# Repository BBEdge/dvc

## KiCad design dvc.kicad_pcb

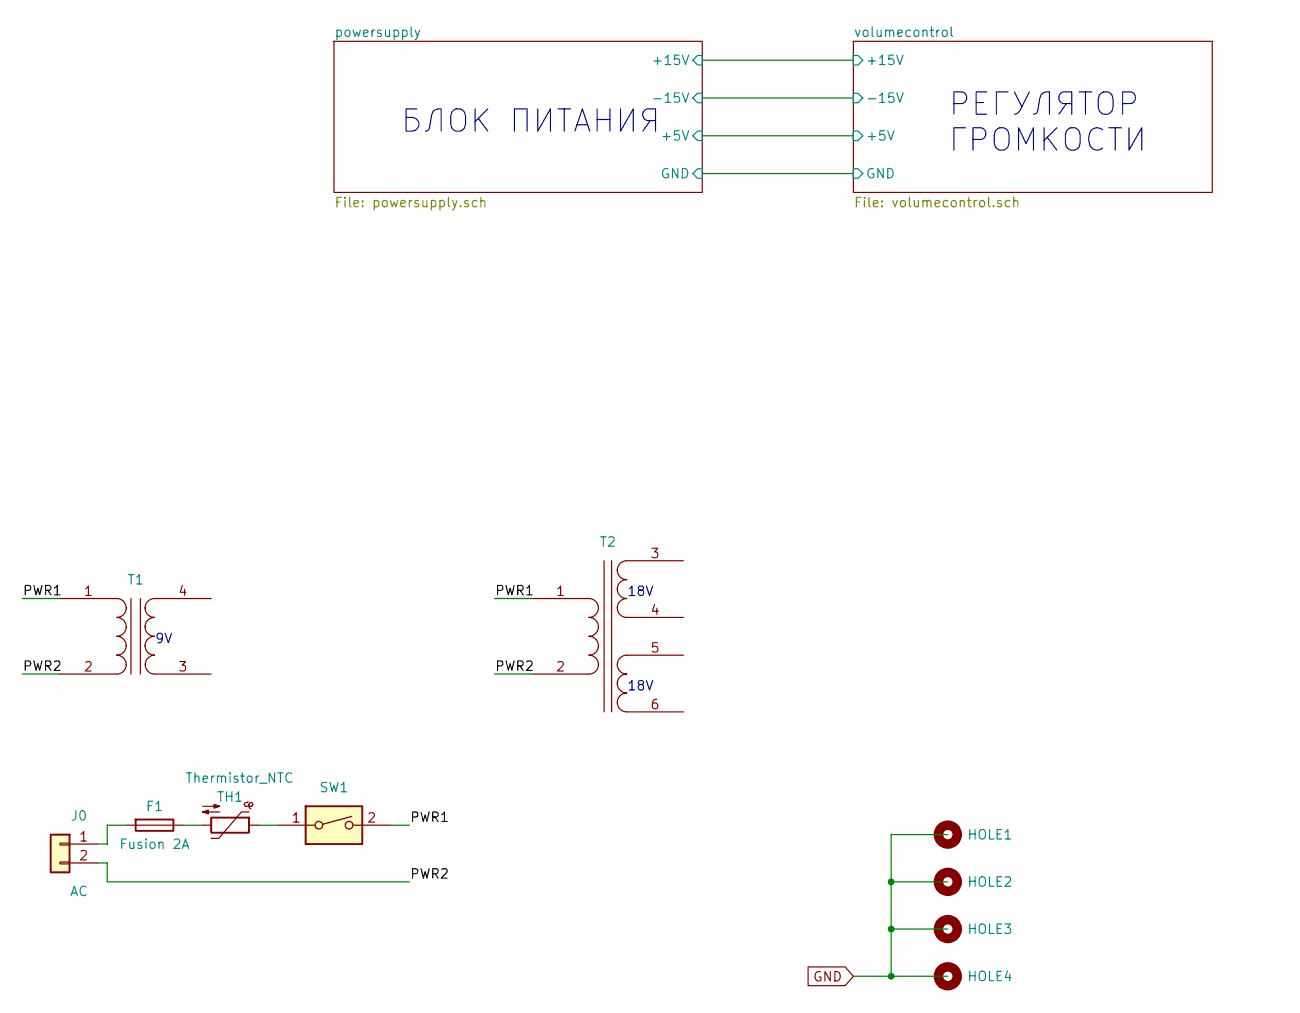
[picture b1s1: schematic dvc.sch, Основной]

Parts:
F1: Fusion 2A
H1: HOLE1; MountingHole_3mm_Pad
H2: HOLE2; MountingHole_3mm_Pad
H3: HOLE3; MountingHole_3mm_Pad
H4: HOLE4; MountingHole_3mm_Pad
J0: AC
SW1: SW_DIP_x01
T1: Transformer_1P_1S
T2: Transformer_1P_2S
TH1: Thermistor_NTC

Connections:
unnamed: F1.1, TH1.2
unnamed: F1.2, J0.1
unnamed: J0.2, T1.2 (AB), T2.2 (AB)
unnamed: SW1.1, TH1.1
unnamed: SW1.2, T1.1 (AA), T2.1 (AA)

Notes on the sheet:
РЕГУЛЯТОР ГРОМКОСТИ
БЛОК ПИТАНИЯ
18V

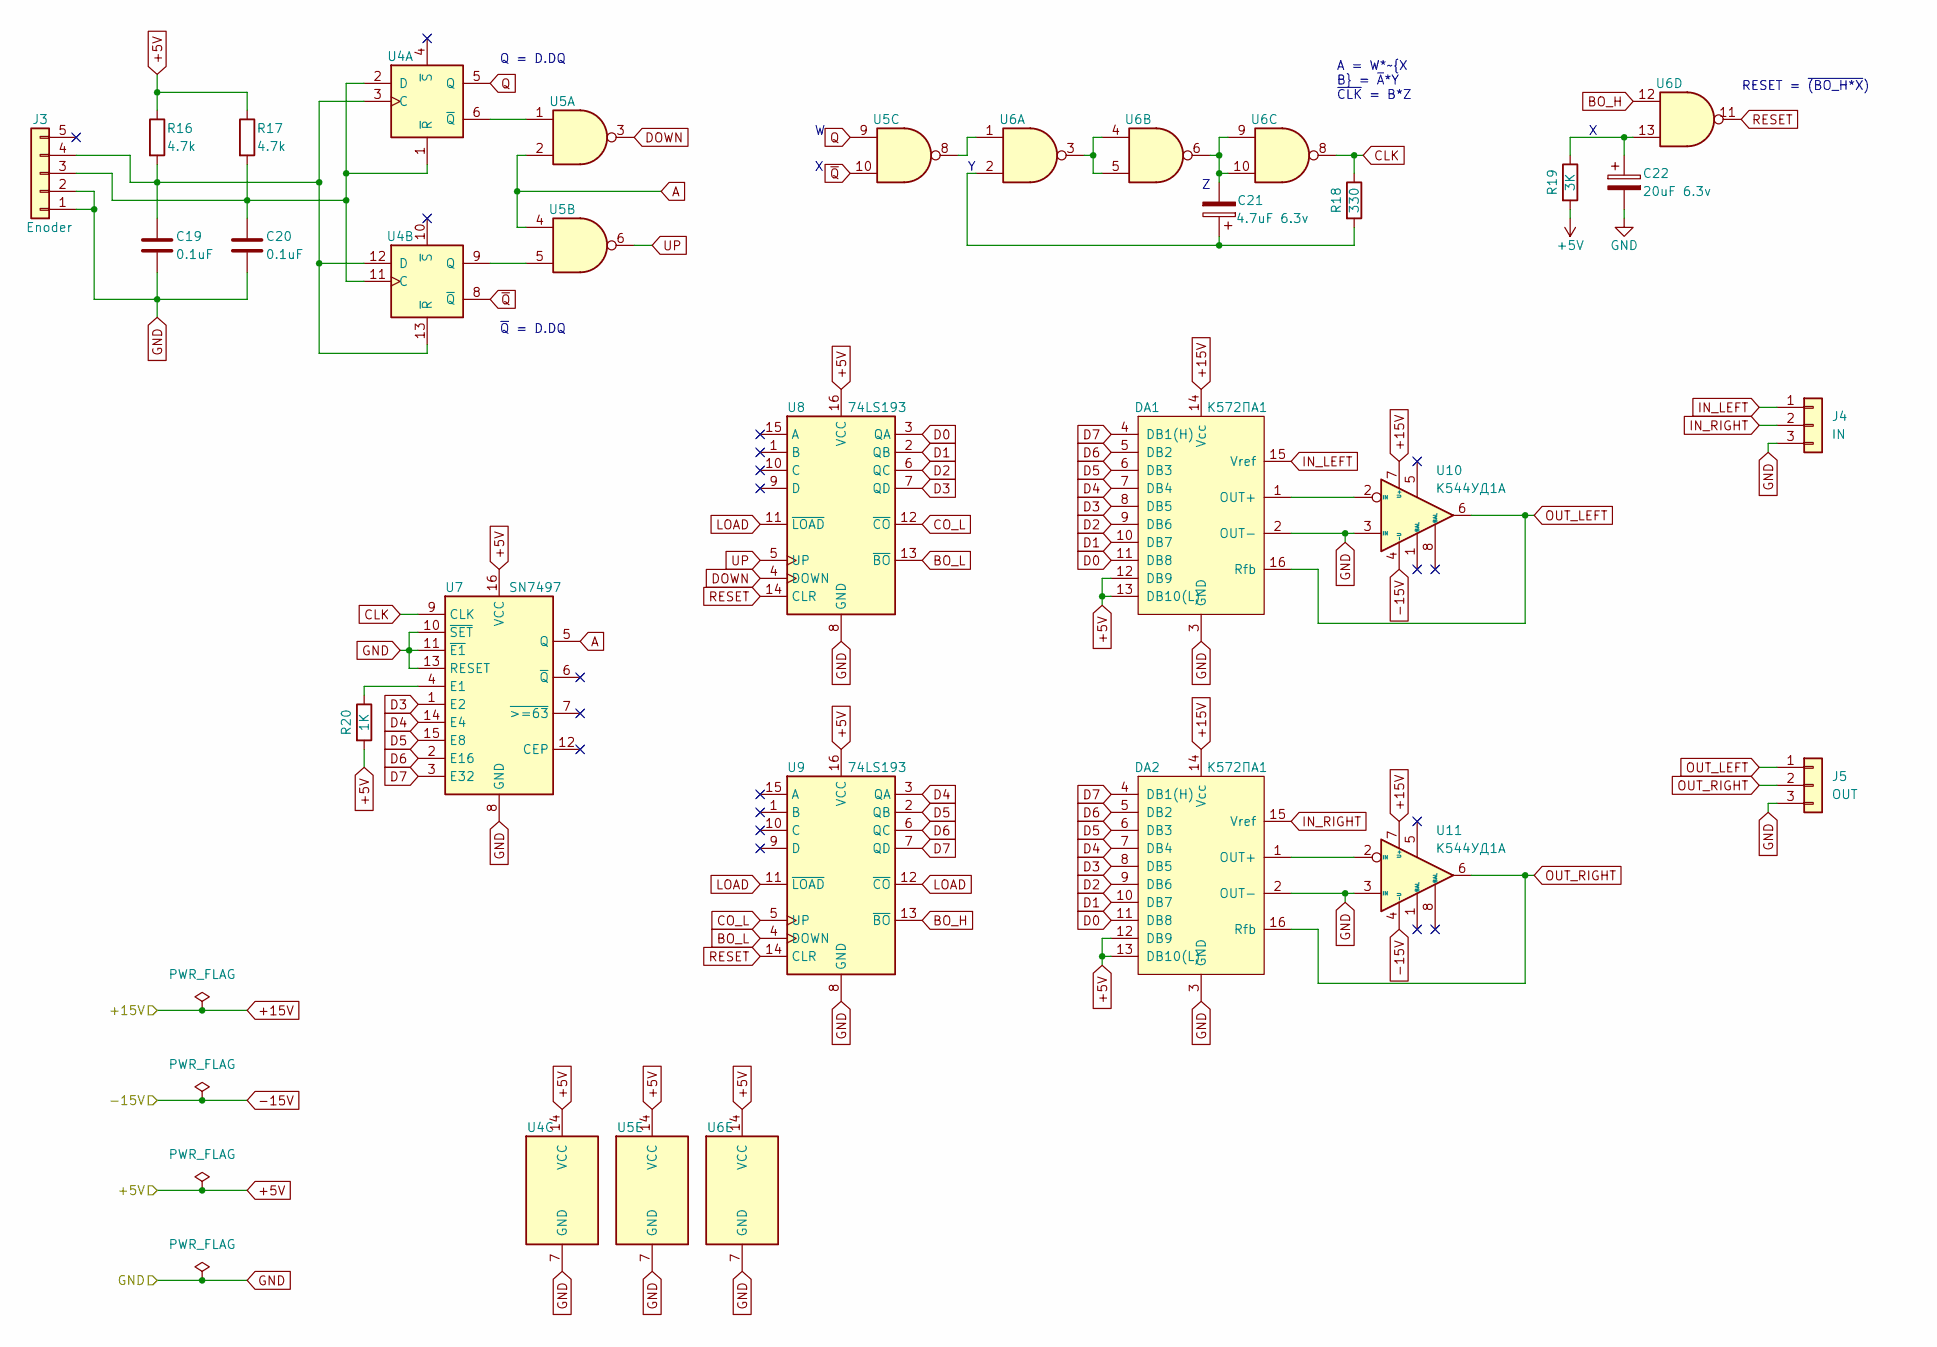
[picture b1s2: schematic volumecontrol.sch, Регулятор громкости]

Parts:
C19, C20: 0.1uF; C_Disc_D4.7mm_W2.5mm_P5.00mm
C21: 4.7uF 6.3v; CP_Radial_D5.0mm_P2.50mm
C22: 20uF 6.3v; CP_Radial_D5.0mm_P2.50mm
DA1, DA2: К572ПА1; DIP-16_W7.62mm_LongPads
J3: Enoder; JST_EH_B5B-EH-A_1x05_P2.50mm_Vertical
J4: IN; JST_EH_B3B-EH-A_1x03_P2.50mm_Vertical
J5: OUT; JST_EH_B3B-EH-A_1x03_P2.50mm_Vertical
R16, R17: 4.7k; R_Axial_DIN0207_L6.3mm_D2.5mm_P10.16mm_Horizontal
R18: 330; R_Axial_DIN0207_L6.3mm_D2.5mm_P10.16mm_Horizontal
R19: 3K; R_Axial_DIN0207_L6.3mm_D2.5mm_P10.16mm_Horizontal
R20: 1K; R_Axial_DIN0207_L6.3mm_D2.5mm_P10.16mm_Horizontal
U4: 74LS74; DIP-14_W7.62mm_LongPads
U5, U6: 74LS00; DIP-14_W7.62mm_LongPads
U7: SN7497; DIP-16_W7.62mm_LongPads
U8, U9: 74LS193; DIP-16_W7.62mm_LongPads
U10, U11: К544УД1А; DIP-8_W7.62mm_LongPads

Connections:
+5V: DA1.12 (DB9), DA1.13 (DB10(L)), DA2.12 (DB9), DA2.13 (DB10(L)), R16.1, R17.1, R19.2, R20.2, U4.14 (VCC), U5.14 (VCC), U6.14 (VCC), U7.16 (VCC), U8.16 (VCC), U9.16 (VCC); also elsewhere on the board
+15V: DA1.14 (Vcc), DA2.14 (Vcc), U10.7 (U+), U11.7 (U+); also elsewhere on the board
-15V: U10.4 (-U), U11.4 (-U); also elsewhere on the board
A: U5.2, U5.4, U7.5 (Q)
BO_H: U6.12, U9.13 (~BO)
BO_L: U8.13 (~BO), U9.4 (DOWN)
CLK: R18.1, U6.8, U7.9 (CLK)
CO_L: U8.12 (~CO), U9.5 (UP)
D0: DA1.11 (DB8), DA2.11 (DB8), U8.3 (QA)
D1: DA1.10 (DB7), DA2.10 (DB7), U8.2 (QB)
D2: DA1.9 (DB6), DA2.9 (DB6), U8.6 (QC)
D3: DA1.8 (DB5), DA2.8 (DB5), U7.1 (E2), U8.7 (QD)
D4: DA1.7 (DB4), DA2.7 (DB4), U7.14 (E4), U9.3 (QA)
D5: DA1.6 (DB3), DA2.6 (DB3), U7.15 (E8), U9.2 (QB)
D6: DA1.5 (DB2), DA2.5 (DB2), U7.2 (E16), U9.6 (QC)
D7: DA1.4 (DB1(H)), DA2.4 (DB1(H)), U7.3 (E32), U9.7 (QD)
DOWN: U5.3, U8.4 (DOWN)
GND: C19.2, C20.2, C22.2, DA1.2 (OUT-), DA1.3 (GND), DA2.2 (OUT-), DA2.3 (GND), J3.1, J3.2, J4.3, J5.3, U4.7 (GND), U5.7 (GND), U6.7 (GND), U7.8 (GND), U7.10 (~SET), U7.11 (~E1), U7.13 (RESET), U8.8 (GND), U9.8 (GND), U10.3 (IN), U11.3 (IN); also elsewhere on the board
IN_LEFT: DA1.15 (Vref), J4.1
IN_RIGHT: DA2.15 (Vref), J4.2
LOAD: U8.11 (~LOAD), U9.11 (~LOAD), U9.12 (~CO)
unnamed: C19.1, J3.4, R16.2, U4.3 (C), U4.12 (D), U4.13 (~R)
unnamed: C20.1, J3.3, R17.2, U4.1 (~R), U4.2 (D), U4.11 (C)
unnamed: C21.1, R18.2, U6.2
unnamed: C21.2, U6.6, U6.9, U6.10
unnamed: C22.1, R19.1, U6.13
unnamed: DA1.1 (OUT+), U10.2 (IN)
unnamed: DA2.1 (OUT+), U11.2 (IN)
unnamed: R20.1, U7.4 (E1)
unnamed: U4.6 (~Q), U5.1
unnamed: U4.9 (Q), U5.5
unnamed: U5.8, U6.1
unnamed: U6.3, U6.4, U6.5
OUT_LEFT: DA1.16 (Rfb), J5.1, U10.6
OUT_RIGHT: DA2.16 (Rfb), J5.2, U11.6
Q: U4.5 (Q), U5.9
RESET: U6.11, U8.14 (CLR), U9.14 (CLR)
UP: U5.6, U8.5 (UP)
~Q: U4.8 (~Q), U5.10

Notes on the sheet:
A = W*~X B = ~A~*Y ~CLK~ = B*Z
RESET = ~(BO_H*X)
Q = D.DQ
~Q~ = D.DQ

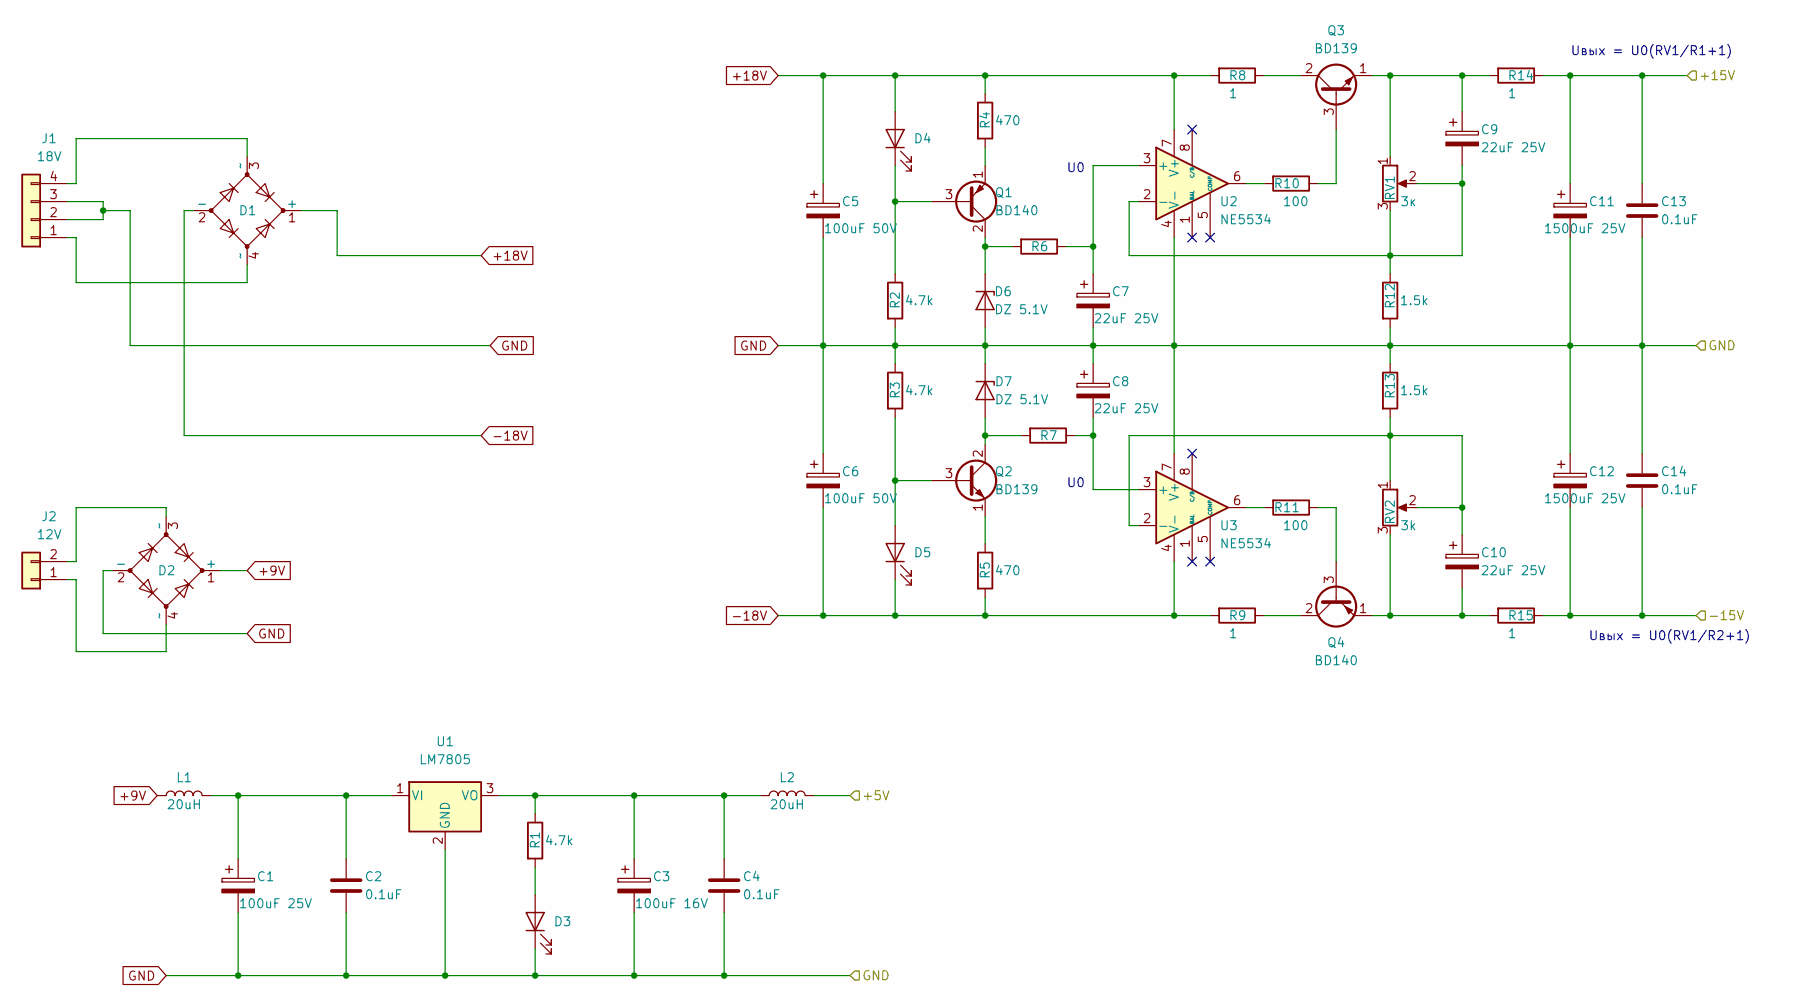
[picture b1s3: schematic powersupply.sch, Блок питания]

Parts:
C1: 100uF 25V; CP_Radial_D5.0mm_P2.50mm
C2, C4, C13, C14: 0.1uF; C_Disc_D4.7mm_W2.5mm_P5.00mm
C3: 100uF 16V; CP_Radial_D5.0mm_P2.50mm
C5, C6: 100uF 50V; CP_Radial_D5.0mm_P2.50mm
C7, C8, C9, C10: 22uF 25V; CP_Radial_D5.0mm_P2.50mm
C11, C12: 1500uF 25V; CP_Radial_D10.0mm_P5.00mm
D1, D2: D_Bridge_+-AA; Diode_Bridge_Round_D9.0mm
D3, D4, D5: LED; LED_D3.0mm
D6, D7: DZ 5.1V; D_T-1_P10.16mm_Horizontal
J1: 18V; JST_EH_B4B-EH-A_1x04_P2.50mm_Vertical
J2: 12V; JST_EH_B2B-EH-A_1x02_P2.50mm_Vertical
L1, L2: 20uH; L_Axial_L7.0mm_D3.3mm_P12.70mm_Horizontal_Fastron_MICC
Q1, Q4: BD140; TO-126-3_Vertical
Q2, Q3: BD139; TO-126-3_Vertical
R1, R2, R3: 4.7k; R_Axial_DIN0207_L6.3mm_D2.5mm_P10.16mm_Horizontal
R4, R5: 470; R_Axial_DIN0207_L6.3mm_D2.5mm_P10.16mm_Horizontal
R6, R7: R; R_Axial_DIN0207_L6.3mm_D2.5mm_P10.16mm_Horizontal
R8, R9, R14, R15: 1; R_Axial_DIN0207_L6.3mm_D2.5mm_P10.16mm_Horizontal
R10, R11: 100; R_Axial_DIN0207_L6.3mm_D2.5mm_P10.16mm_Horizontal
R12, R13: 1.5k; R_Axial_DIN0207_L6.3mm_D2.5mm_P10.16mm_Horizontal
RV1: 3к; Potentiometer_Piher_PT-6-V_Vertical
RV2: 3k; Potentiometer_Piher_PT-6-V_Vertical
U1: LM7805; TO-220-3_Vertical
U2, U3: NE5534; DIP-8_W7.62mm_LongPads

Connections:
+5V: L2.2; also elsewhere on the board
+9V: D2.1 (+), L1.1
+15V: C11.1, C13.1, R14.1; also elsewhere on the board
+18V: C5.1, D1.1 (+), D4.2 (A), R4.1, R8.2, U2.7 (V+)
-15V: C12.2, C14.2, R15.1; also elsewhere on the board
-18V: C6.2, D1.2 (-), D5.1 (K), R5.2, R9.2, U3.4 (V-)
GND: C1.2, C2.2, C3.2, C4.2, C5.2, C6.1, C7.2, C8.1, C11.2, C12.1, C13.2, C14.1, D2.2 (-), D3.1 (K), D6.2 (A), D7.1 (K), J1.2, J1.3, R2.2, R3.1, R12.2, R13.1, U1.2 (GND), U2.4 (V-), U3.7 (V+); also elsewhere on the board
unnamed: C1.1, C2.1, L1.2, U1.1 (VI)
unnamed: C3.1, C4.1, L2.1, R1.1, U1.3 (VO)
unnamed: C7.1, R6.1, U2.3 (+)
unnamed: C8.2, R7.1, U3.3 (+)
unnamed: C9.1, Q3.1 (E), R14.2, RV1.1
unnamed: C9.2, R12.1, RV1.2, RV1.3, U2.2 (-)
unnamed: C10.1, R13.2, RV2.1, RV2.2, U3.2 (-)
unnamed: C10.2, Q4.1 (E), R15.2, RV2.3
unnamed: D1.3 (~~), J1.4
unnamed: D1.4 (~~), J1.1
unnamed: D2.3 (~~), J2.2
unnamed: D2.4 (~~), J2.1
unnamed: D3.2 (A), R1.2
unnamed: D4.1 (K), Q1.3 (B), R2.1
unnamed: D5.2 (A), Q2.3 (B), R3.2
unnamed: D6.1 (K), Q1.2 (C), R6.2
unnamed: D7.2 (A), Q2.2 (C), R7.2
unnamed: Q1.1 (E), R4.2
unnamed: Q2.1 (E), R5.1
unnamed: Q3.2 (C), R8.1
unnamed: Q3.3 (B), R10.1
unnamed: Q4.2 (C), R9.1
unnamed: Q4.3 (B), R11.1
unnamed: R10.2, U2.6
unnamed: R11.2, U3.6

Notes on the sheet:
Uвых = U0(RV1/R1+1)
Uвых = U0(RV1/R2+1)

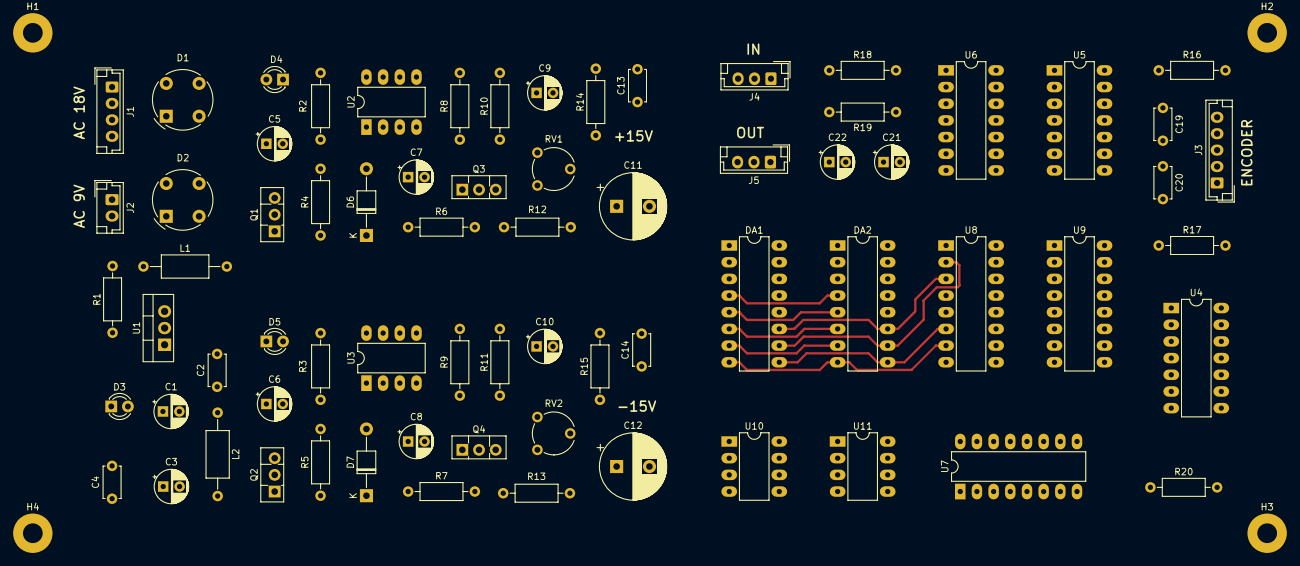
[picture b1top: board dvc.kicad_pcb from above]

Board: 2 copper layers, 75 parts (0 on the bottom side), 67 nets.
